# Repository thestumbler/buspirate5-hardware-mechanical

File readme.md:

# Bus Pirate 5, Mechanical Envelope Drawing

This repo has some scripts to enable semi-automatic preparation of
mechanical envelope drawing of the Bus Pirate 5 enclosure. 

## Background

The enclosure is designed in OpenSCAD. Getting 2D dimension drawings out
of OpenSCAD, while possible, is awkward ( see this [repo](
https://github.com/pwpearson/dimensional-drawings.git) for example ).
It is straightforward to make an XY projection or cut of an object. 
And KiCad has basic dimensioning for several versions now. So the
approach taken is

(1) create projections using OpenSCAD design
(2) save as DXF files, import into KiCad
(3) add dimensioning in KiCad

## OpenSCAD Projections

The file `make2d.scad` contains the for projecting the
different views. The code is organized as follows:

* module fiducial()
* module scad2kicad()
* module scad2kicad_sides()
* module project()
* module project_aux_side()
* module project_usb_side()
* // Main Slicing Code...

In summary, this requires the following 
operations (details are in the code):

* X-Y translation
* Mirroring
* Rotation
* Matching origin

This code could be put directly in the SCAD file. But there are several
versions to deal with, and it would be nice to keep this code separate.
The code is substantially independent, although it reaches into the
enclosure file to get the objects needed.

The only problem encountered with this approach is with OpenSCAD
importing of modules.

* If you `include` a file, you pickup all the modules and variables, but
  you also get any objects that are drawn in the main code.

* If you `use` a file, you get all the modules, any objects are not
  drawn, but you don't get the variables.

I don't have a solution for this. What I did was a compromise. I moved
all the parameters in the enclosure design to a file `params.scad`. 
If this is adopted, then all the versions of the enclosure would need to
carve out the variables into separate parameter files.

One other option is to organize the enclosure files so they don't create
any mainline objects without a control flag. This makes is easy to
include the files as-is, and use flags in the user customizer panel. See
`make2d.scad` for an example of this.

## KiCad Import

Importing the DXF files into KiCad is made easy by positioning the XY
projections in OpenSCAD so they match the exact placement of the PCB in
KiCAD. You can just import the files referenced to (0,0) and there is no
need to use interactive placement.

Four new layers are created as follows:

* User1  Bottom XY projection
* User2  Top and Sides projections
* User3  Bottom dimensions
* User4  Top and Sides dimensions

Dimensions are made by hand. 

## Revisions

All these four layers are kept in a separete PCB design `mech`. This
deisng only has four layers, the four user layers. If you make a new
BusPirate revision, you to the `append board` operation to add these to
the design.

If there are changes to the enclosure design, you have to remake the DXF
files and reimport them into KiCad. For most changes, it is easy to 
tweak the dimension layers to match any changes. The shell script
`make2d.sh` creates all four DXF files at once. 

As currently coded, you meed to manually edit the include statement in
make2d.scad (the target file of an include/use cannot be a variable).

# Resources

- [Download the latest firmware build](https://forum.buspirate.com/t/bus-pirate-5-auto-build-main-branch/20/99999)
- [Get help and chat in the forum](https://forum.buspirate.com/)
- [Firmware documentation](https://firmware.buspirate.com/) ([source](https://github.com/DangerousPrototypes/BusPirate5-docs-firmware))
- [Hardware documentation](https://hardware.buspirate.com/) ([source](https://github.com/DangerousPrototypes/BusPirate5-docs-hardware))
- [Hardware repo](https://github.com/DangerousPrototypes/BusPirate5-hardware)
- [Firmware repo](https://github.com/DangerousPrototypes/BusPirate5-firmware)

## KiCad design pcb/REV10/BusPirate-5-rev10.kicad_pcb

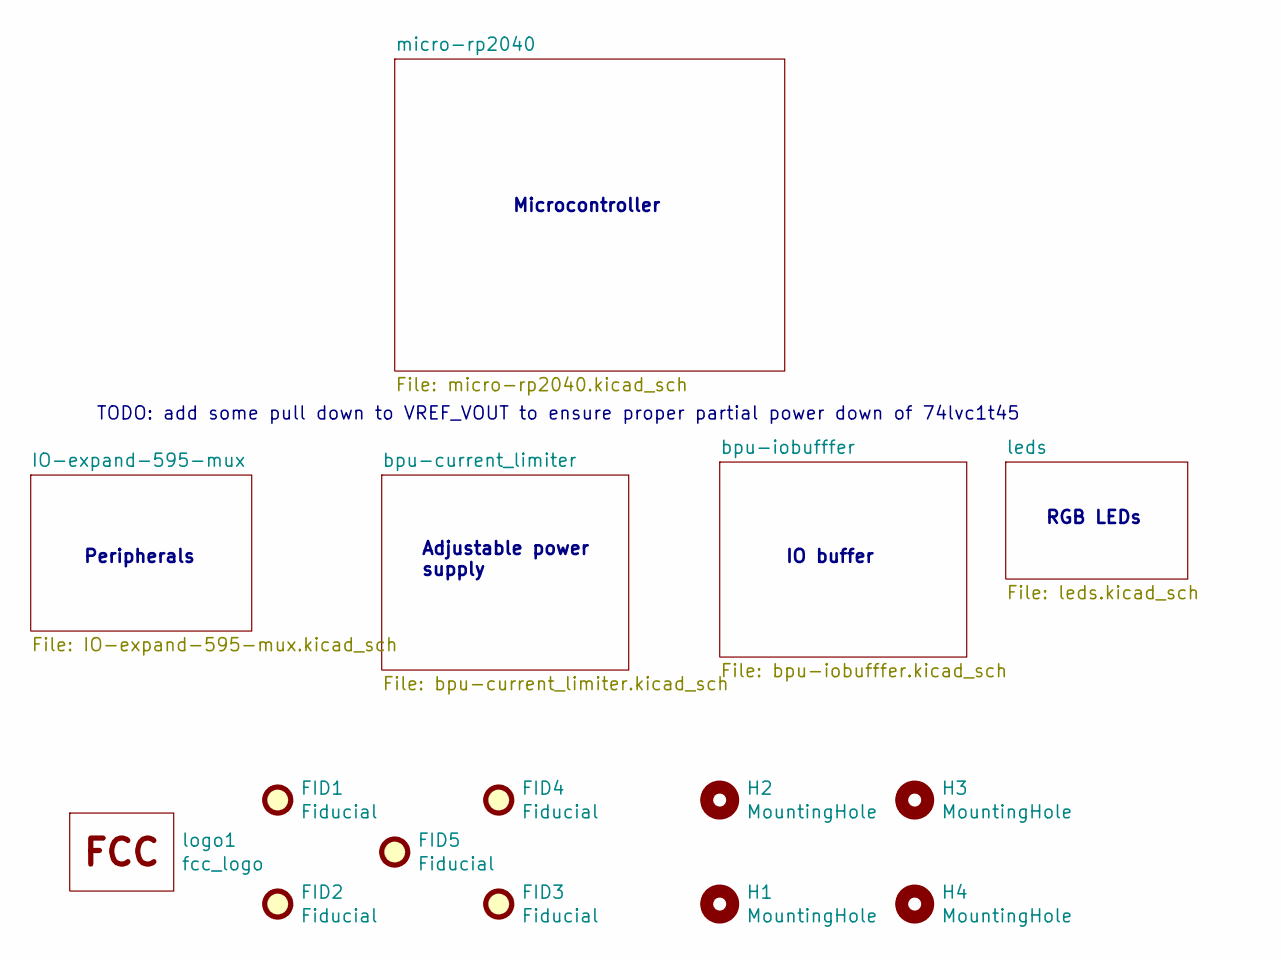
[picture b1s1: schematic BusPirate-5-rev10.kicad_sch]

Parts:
FID1, FID2, FID3, FID4, FID5: Fiducial; Fiducial_1mm_Mask2mm
H1, H2, H3, H4: MountingHole; MountingHole_3.2mm_M3
logo1: fcc_logo; logo_fcc

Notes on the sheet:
Microcontroller
Adjustable power supply
TODO: add some pull down to VREF_VOUT to ensure proper partial power down of 74lvc1t45
IO buffer
Peripherals
RGB LEDs

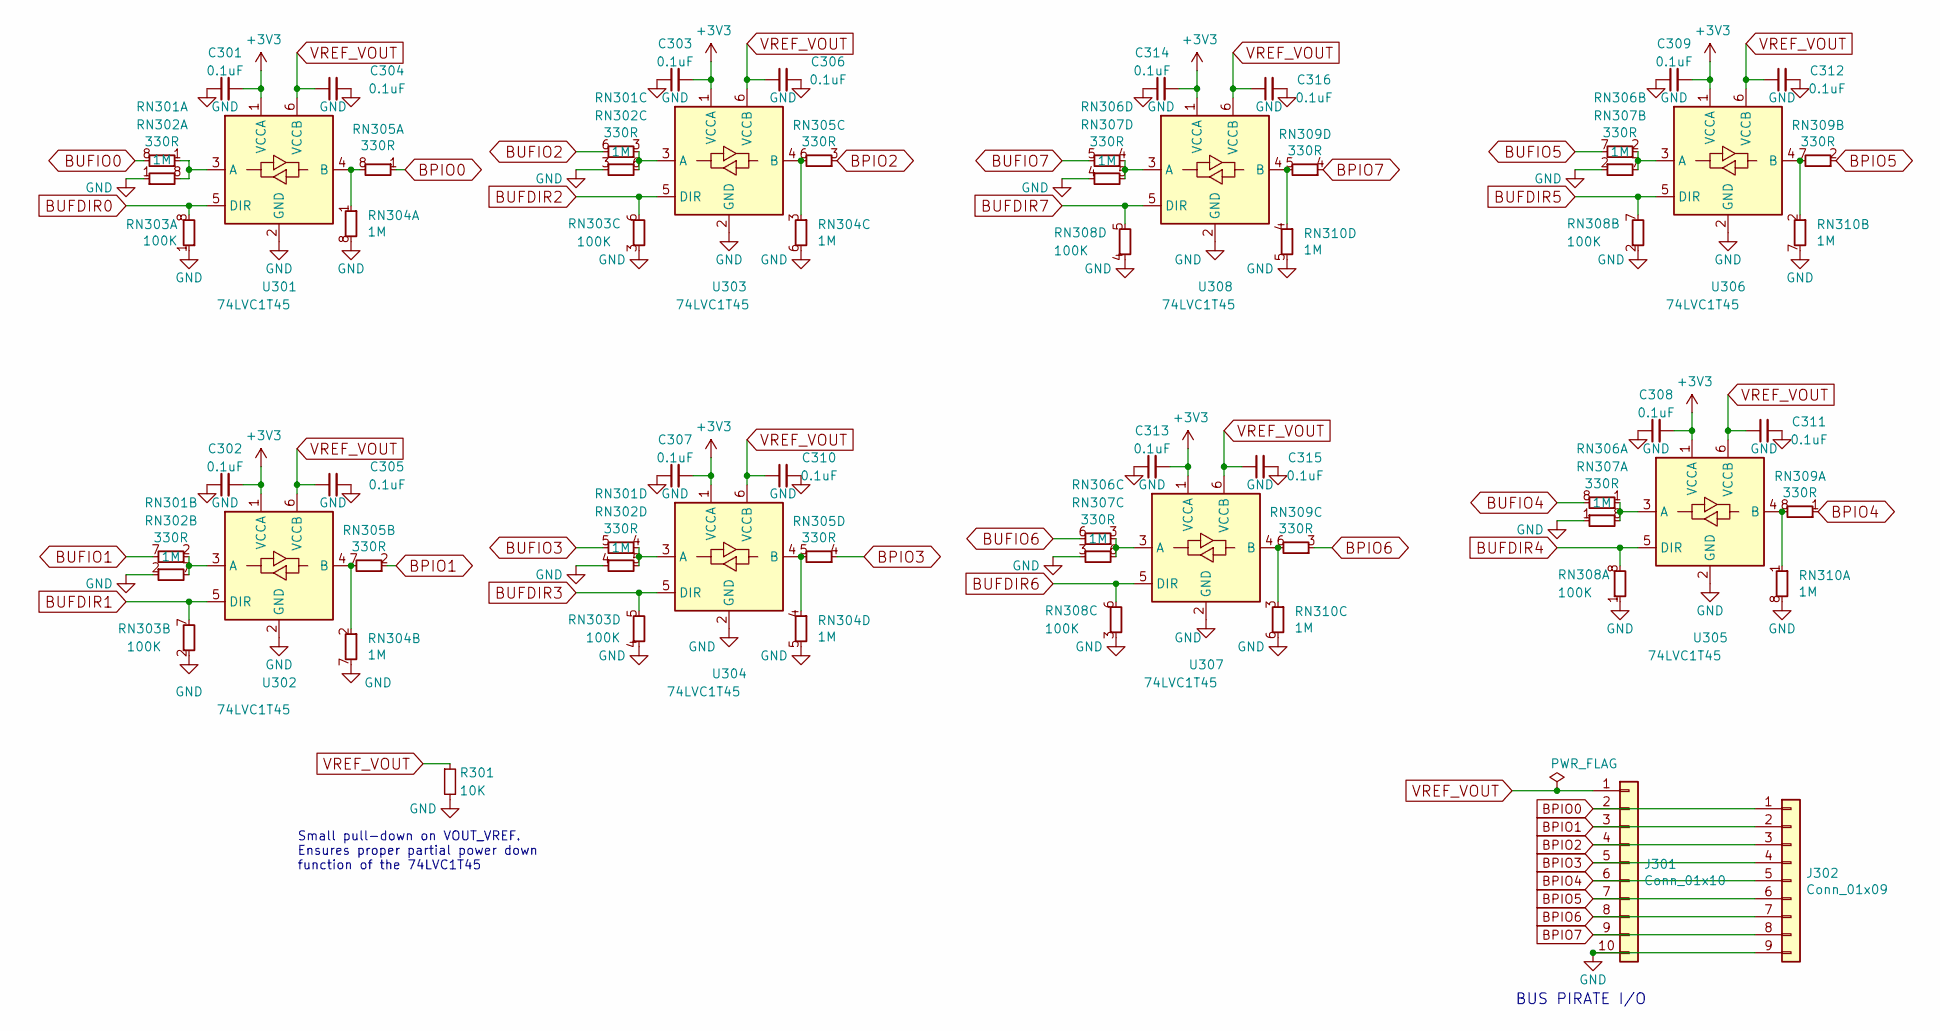
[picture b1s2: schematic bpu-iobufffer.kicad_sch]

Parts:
C301, C302, C303, C304, C305, C306, C307, C308, C309, C310, C311, C312, C313, C314, C315, C316: 0.1uF; C_0402_1005Metric
J301: Conn_01x10; PinHeader_1x10_P2.54mm_Vertical
J302: Conn_01x09; JST_SH_SM09B-SRSS-TB_1x09-1MP_P1.00mm_Horizontal
R301: 10K; R_0402_1005Metric
RN301, RN305, RN306, RN309: 330R; R_Array_Convex_4x0402
RN302, RN304, RN307, RN310: 1M; R_Array_Convex_4x0402
RN303, RN308: 100K; R_Array_Convex_4x0402
U301, U302, U303, U304, U305, U306, U307, U308: 74LVC1T45; SOT-363_SC-70-6

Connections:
+3V3: C301.2, C302.2, C303.2, C307.2, C308.2, C309.2, C313.2, C314.2, U301.1 (VCCA), U302.1 (VCCA), U303.1 (VCCA), U304.1 (VCCA), U305.1 (VCCA), U306.1 (VCCA), U307.1 (VCCA), U308.1 (VCCA); also elsewhere on the board
BPIO0: J301.2, J302.1, RN305.1 (R1.1); also elsewhere on the board
BPIO1: J301.3, J302.2, RN305.2 (R1.1); also elsewhere on the board
BPIO2: J301.4, J302.3, RN305.3 (R1.1); also elsewhere on the board
BPIO3: J301.5, J302.4, RN305.4 (R1.1); also elsewhere on the board
BPIO4: J301.6, J302.5, RN309.1 (R1.1); also elsewhere on the board
BPIO5: J301.7, J302.6, RN309.2 (R1.1); also elsewhere on the board
BPIO6: J301.8, J302.7, RN309.3 (R1.1); also elsewhere on the board
BPIO7: J301.9, J302.8, RN309.4 (R1.1); also elsewhere on the board
BUFDIR0: RN303.8 (R1.8), U301.5 (DIR); also elsewhere on the board
BUFDIR1: RN303.7 (R1.8), U302.5 (DIR); also elsewhere on the board
BUFDIR2: RN303.6 (R1.8), U303.5 (DIR); also elsewhere on the board
BUFDIR3: RN303.5 (R1.8), U304.5 (DIR); also elsewhere on the board
BUFDIR4: RN308.8 (R1.8), U305.5 (DIR); also elsewhere on the board
BUFDIR5: RN308.7 (R1.8), U306.5 (DIR); also elsewhere on the board
BUFDIR6: RN308.6 (R1.8), U307.5 (DIR); also elsewhere on the board
BUFDIR7: RN308.5 (R1.8), U308.5 (DIR); also elsewhere on the board
BUFIO0: RN301.8 (R1.8); also elsewhere on the board
BUFIO1: RN301.7 (R1.8); also elsewhere on the board
BUFIO2: RN301.6 (R1.8); also elsewhere on the board
BUFIO3: RN301.5 (R1.8); also elsewhere on the board
BUFIO4: RN306.8 (R1.8); also elsewhere on the board
BUFIO5: RN306.7 (R1.8); also elsewhere on the board
BUFIO6: RN306.6 (R1.8); also elsewhere on the board
BUFIO7: RN306.5 (R1.8); also elsewhere on the board
GND: C301.1, C302.1, C303.1, C304.2, C305.2, C306.2, C307.1, C308.1, C309.1, C310.2, C311.2, C312.2, C313.1, C314.1, C315.2, C316.2, J301.10, J302.9, R301.2, RN302.1 (R1.1), RN302.2 (R1.1), RN302.3 (R1.1), RN302.4 (R1.1), RN303.1 (R1.1), RN303.2 (R1.1), RN303.3 (R1.1), RN303.4 (R1.1), RN304.5 (R1.8), RN304.6 (R1.8), RN304.7 (R1.8), RN304.8 (R1.8), RN307.1 (R1.1), RN307.2 (R1.1), RN307.3 (R1.1), RN307.4 (R1.1), RN308.1 (R1.1), RN308.2 (R1.1), RN308.3 (R1.1), RN308.4 (R1.1), RN310.5 (R1.8), RN310.6 (R1.8), RN310.7 (R1.8), RN310.8 (R1.8), U301.2 (GND), U302.2 (GND), U303.2 (GND), U304.2 (GND), U305.2 (GND), U306.2 (GND), U307.2 (GND), U308.2 (GND); also elsewhere on the board
unnamed: RN301.1 (R1.1), RN302.8 (R1.8), U301.3 (A)
unnamed: RN301.2 (R1.1), RN302.7 (R1.8), U302.3 (A)
unnamed: RN301.3 (R1.1), RN302.6 (R1.8), U303.3 (A)
unnamed: RN301.4 (R1.1), RN302.5 (R1.8), U304.3 (A)
unnamed: RN304.1 (R1.1), RN305.8 (R1.8), U301.4 (B)
unnamed: RN304.2 (R1.1), RN305.7 (R1.8), U302.4 (B)
unnamed: RN304.3 (R1.1), RN305.6 (R1.8), U303.4 (B)
unnamed: RN304.4 (R1.1), RN305.5 (R1.8), U304.4 (B)
unnamed: RN306.1 (R1.1), RN307.8 (R1.8), U305.3 (A)
unnamed: RN306.2 (R1.1), RN307.7 (R1.8), U306.3 (A)
unnamed: RN306.3 (R1.1), RN307.6 (R1.8), U307.3 (A)
unnamed: RN306.4 (R1.1), RN307.5 (R1.8), U308.3 (A)
unnamed: RN309.8 (R1.8), RN310.1 (R1.1), U305.4 (B)
unnamed: RN309.7 (R1.8), RN310.2 (R1.1), U306.4 (B)
unnamed: RN309.6 (R1.8), RN310.3 (R1.1), U307.4 (B)
unnamed: RN309.5 (R1.8), RN310.4 (R1.1), U308.4 (B)
VREF_VOUT: C304.1, C305.1, C306.1, C310.1, C311.1, C312.1, C315.1, C316.1, J301.1, R301.1, U301.6 (VCCB), U302.6 (VCCB), U303.6 (VCCB), U304.6 (VCCB), U305.6 (VCCB), U306.6 (VCCB), U307.6 (VCCB), U308.6 (VCCB); also elsewhere on the board

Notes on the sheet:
Small pull-down on VOUT_VREF. Ensures proper partial power down function of the 74LVC1T45
BUS PIRATE I/O

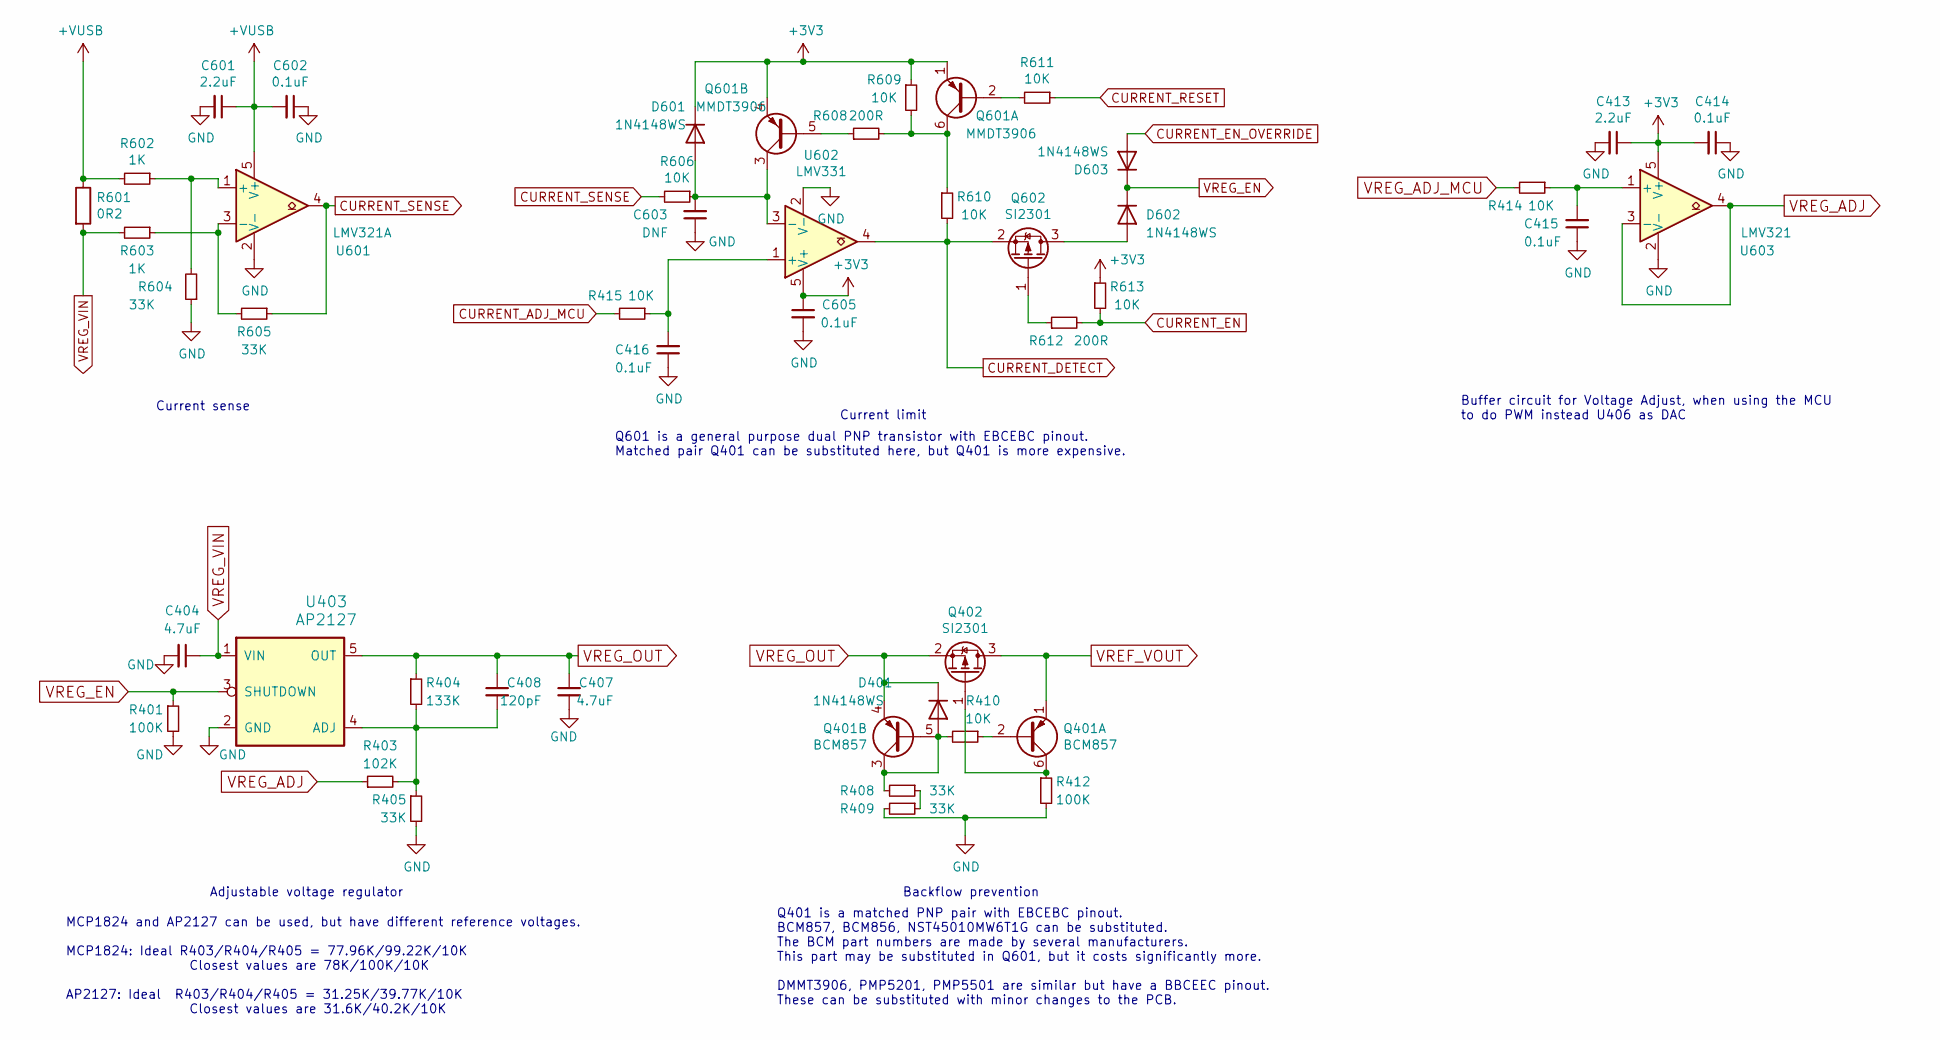
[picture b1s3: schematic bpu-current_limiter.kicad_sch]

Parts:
C404, C407: 4.7uF; C_0402_1005Metric
C408: 120pF; C_0402_1005Metric
C413, C601: 2.2uF; C_0402_1005Metric
C414, C415, C416, C602, C605: 0.1uF; C_0402_1005Metric
C603: DNF; C_0402_1005Metric
D401, D601, D602, D603: 1N4148WS; D_SOD-523
Q401: BCM857; SOT-363_SC-70-6
Q402, Q602: SI2301; SOT-523
Q601: MMDT3906; SOT-363_SC-70-6
R401, R412: 100K; R_0402_1005Metric
R403: 102K; R_0402_1005Metric
R404: 133K; R_0402_1005Metric
R405, R408, R409, R604, R605: 33K; R_0402_1005Metric
R410, R414, R415, R606, R609, R610, R611, R613: 10K; R_0402_1005Metric
R601: 0R2; R_2512_6332Metric_Pad1.40x3.35mm_HandSolder
R602, R603: 1K; R_0402_1005Metric
R608, R612: 200R; R_0402_1005Metric
U403: AP2127; SOT-23-5
U601: LMV321A; SOT-23-5
U602: LMV331; SOT-23-5
U603: LMV321; SOT-23-5

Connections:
+3V3: C413.1, C414.2, C605.1, D601.1 (K), Q601.1 (E1), Q601.4 (E2), R609.1, R613.1, U602.5 (V+), U603.5 (V+); also elsewhere on the board
+VUSB: C601.1, C602.2, R601.1, R602.2, U601.5 (V+); also elsewhere on the board
CURRENT_ADJ_MCU: R415.2; also elsewhere on the board
CURRENT_DETECT: Q602.2 (S), R610.2, U602.4; also elsewhere on the board
CURRENT_EN: R612.2, R613.2; also elsewhere on the board
CURRENT_EN_OVERRIDE: D603.2 (A); also elsewhere on the board
CURRENT_RESET: R611.1; also elsewhere on the board
CURRENT_SENSE: R605.1, R606.2, U601.4; also elsewhere on the board
GND: C404.2, C407.2, C413.2, C414.1, C415.1, C416.1, C601.2, C602.1, C603.1, C605.2, R401.2, R405.2, R409.2, R412.2, R604.1, U403.2 (GND), U601.2 (V-), U602.2 (V-), U603.2 (V-); also elsewhere on the board
unnamed: D401.2 (A), Q401.3 (C2), Q401.5 (B2), R408.2, R410.2
unnamed: C603.2, D601.2 (A), Q601.3 (C2), R606.1, U602.3 (-)
unnamed: D602.2 (A), Q602.3 (D)
unnamed: Q401.2 (B1), R410.1
unnamed: Q401.6 (C1), Q402.1 (G), R412.1
unnamed: Q601.2 (B1), R611.2
unnamed: Q601.6 (C1), R608.2, R609.2, R610.1
unnamed: Q601.5 (B2), R608.1
unnamed: Q602.1 (G), R612.1
unnamed: R408.1, R409.1
unnamed: C408.2, R403.2, R404.2, R405.1, U403.4 (ADJ)
unnamed: R602.1, R604.2, U601.1 (+)
unnamed: R603.1, R605.2, U601.3 (-)
unnamed: C416.2, R415.1, U602.1 (+)
unnamed: C415.2, R414.1, U603.1 (+)
VREF_VOUT: Q401.1 (E1), Q402.3 (D); also elsewhere on the board
VREG_ADJ: R403.1, U603.3 (-), U603.4
VREG_ADJ_MCU: R414.2; also elsewhere on the board
VREG_EN: D602.1 (K), D603.1 (K), R401.1, U403.3 (SHUTDOWN)
VREG_OUT: C407.1, C408.1, D401.1 (K), Q401.4 (E2), Q402.2 (S), R404.1, U403.5 (OUT); also elsewhere on the board
VREG_VIN: C404.1, R601.2, R603.2, U403.1 (VIN)

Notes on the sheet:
Adjustable voltage regulator
Buffer circuit for Voltage Adjust, when using the MCU to do PWM instead U406 as DAC
Current sense
Backflow prevention
MCP1824 and AP2127 can be used, but have different reference voltages. MCP1824: Ideal R403/R404/R405 = 77.96K/99.22K/10K Closest values are 78K/100K/10K AP2127: Ideal R403/R404/R405 = 31.25K/39.77K/10K Closest values are 31.6K/40.2K/10K
Current limit
Q401 is a matched PNP pair with EBCEBC pinout. BCM857, BCM856, NST45010MW6T1G can be substituted. The BCM part numbers are made by several manufacturers. This part may be substituted in Q601, but it costs significantly more. DMMT3906, PMP5201, PMP5501 are similar but have a BBCEEC pinout. These can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
Q601 is a general purpose dual PNP transistor with EBCEBC pinout. Matched pair Q401 can be substituted here, but Q401 is more expensive.

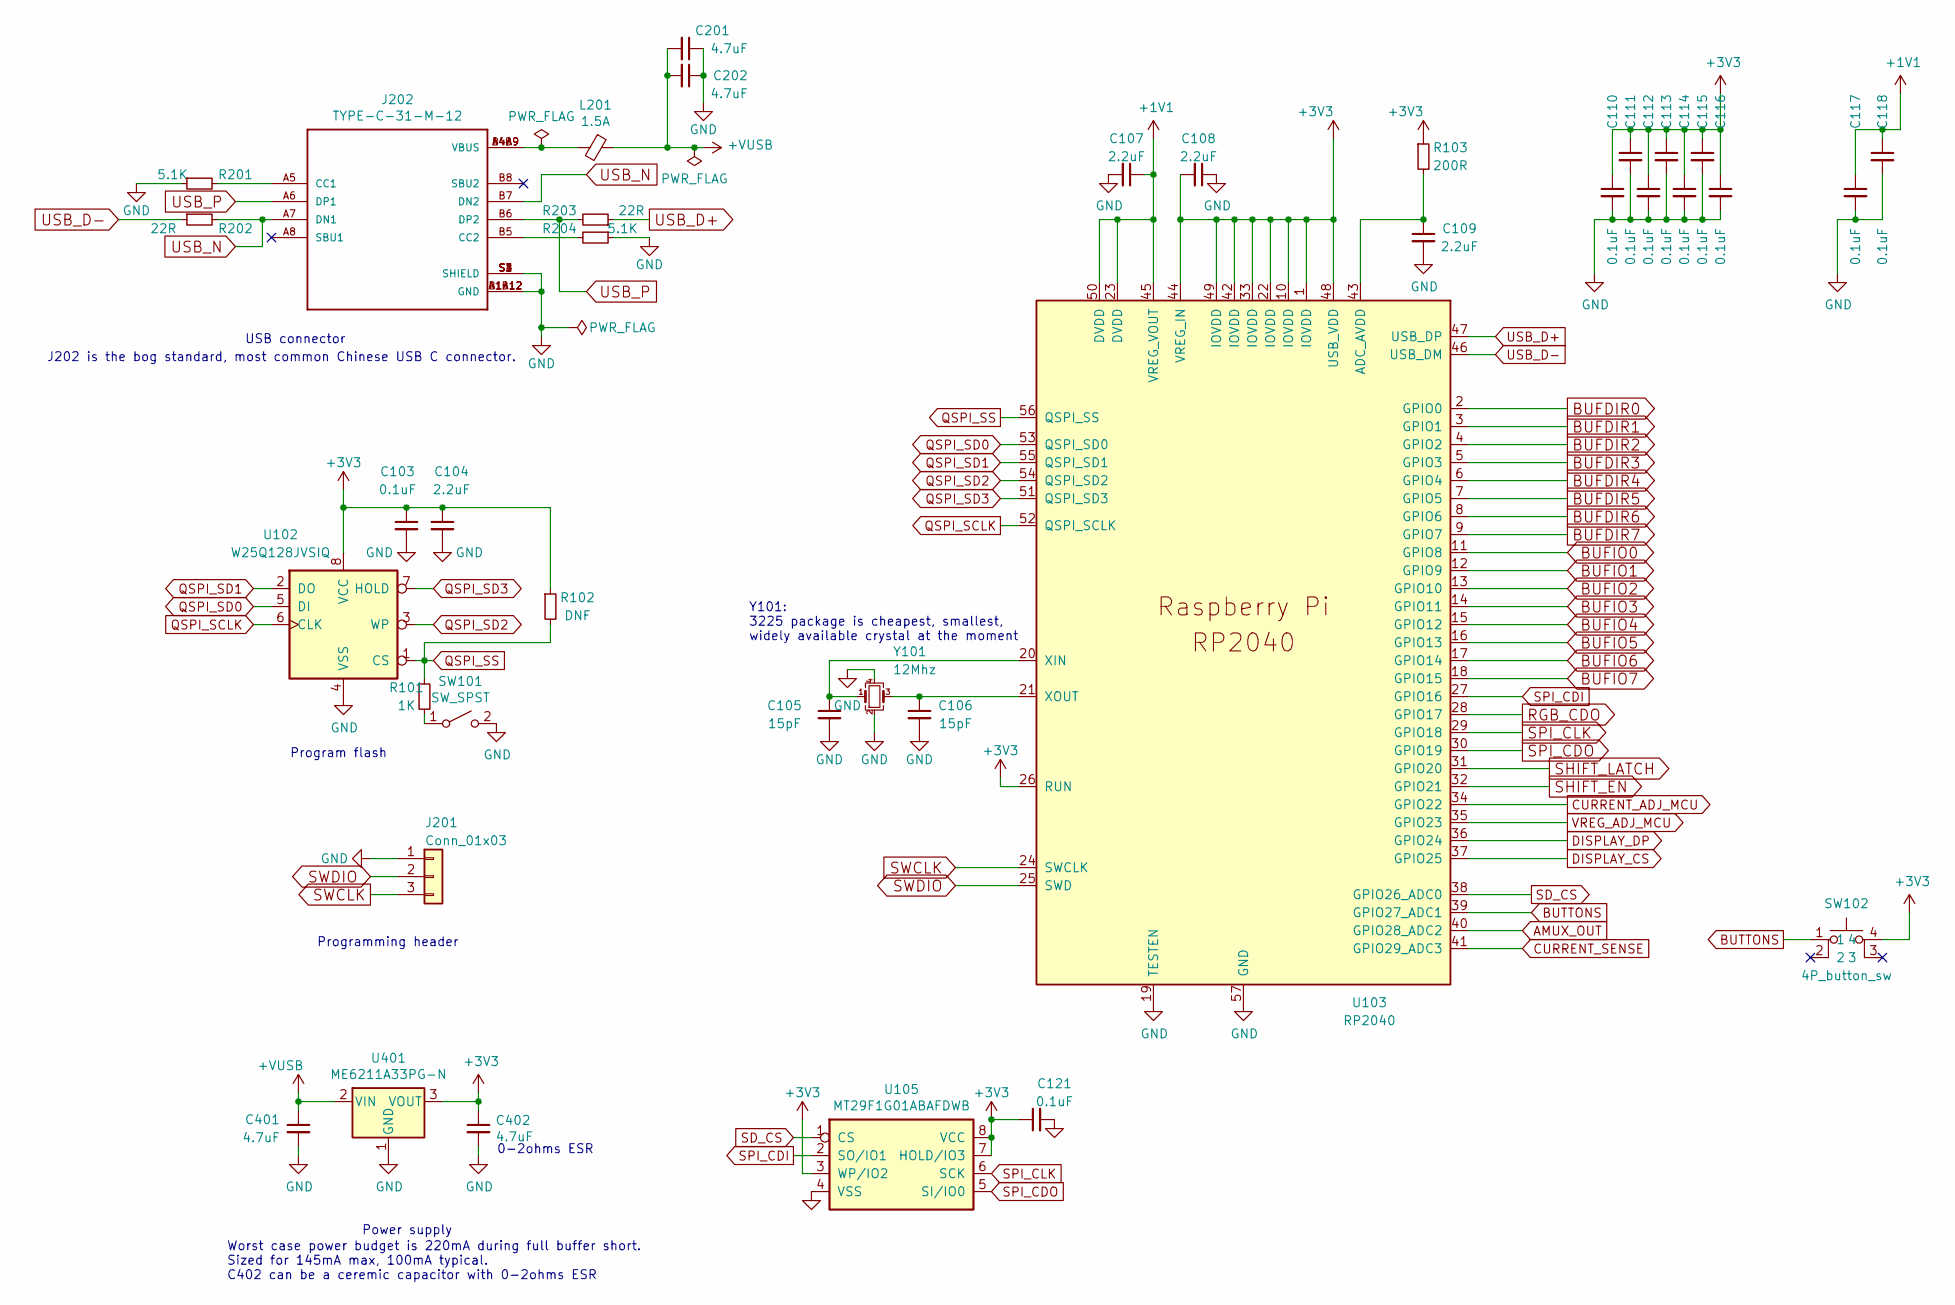
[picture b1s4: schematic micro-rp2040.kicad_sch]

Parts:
C103, C110, C111, C112, C113, C114, C115, C116, C117, C118, C121: 0.1uF; C_0402_1005Metric
C104, C107, C108, C109: 2.2uF; C_0402_1005Metric
C105, C106: 15pF; C_0402_1005Metric
C201, C202, C401, C402: 4.7uF; C_0402_1005Metric
J201: Conn_01x03; PinSocket_1x03_P2.54mm_Vertical
J202: TYPE-C-31-M-12; HRO_TYPE-C-31-M-12
L201: 1.5A; L_0805_2012Metric
R101: 1K; R_0402_1005Metric
R102: DNF; R_0402_1005Metric
R103: 200R; R_0402_1005Metric
R201, R204: 5.1K; R_0402_1005Metric
R202, R203: 22R; R_0402_1005Metric
SW101: SW_SPST; SW_SPST_PTS810
SW102: 4P_button_sw; GT-TC026X-HXXX-LX
U102: W25Q128JVSIQ; SOP-8_5.28x5.23mm_P1.27mm
U103: RP2040; RP2040-QFN-56
U105: MT29F1G01ABAFDWB; U-PDFN-8
U401: ME6211A33PG-N; SOT-89-3
Y101: 12Mhz; Crystal_SMD_3225-4Pin_3.2x2.5mm

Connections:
+1V1: C107.1, C117.1, C118.1, U103.23 (DVDD), U103.45 (VREG_VOUT), U103.50 (DVDD)
+3V3: C103.1, C104.1, C108.2, C110.1, C111.1, C112.1, C113.1, C114.1, C115.1, C116.1, C121.1, C402.1, R102.1, R103.1, SW102.4, U102.8 (VCC), U103.1 (IOVDD), U103.10 (IOVDD), U103.22 (IOVDD), U103.26 (RUN), U103.33 (IOVDD), U103.42 (IOVDD), U103.44 (VREG_IN), U103.48 (USB_VDD), U103.49 (IOVDD), U105.3 (WP/IO2), U105.7 (HOLD/IO3), U105.8 (VCC), U401.3 (VOUT); also elsewhere on the board
+VUSB: C201.2, C202.2, C401.1, L201.1, U401.2 (VIN); also elsewhere on the board
AMUX_OUT: U103.40 (GPIO28_ADC2); also elsewhere on the board
BUFDIR0: U103.2 (GPIO0); also elsewhere on the board
BUFDIR1: U103.3 (GPIO1); also elsewhere on the board
BUFDIR2: U103.4 (GPIO2); also elsewhere on the board
BUFDIR3: U103.5 (GPIO3); also elsewhere on the board
BUFDIR4: U103.6 (GPIO4); also elsewhere on the board
BUFDIR5: U103.7 (GPIO5); also elsewhere on the board
BUFDIR6: U103.8 (GPIO6); also elsewhere on the board
BUFDIR7: U103.9 (GPIO7); also elsewhere on the board
BUFIO0: U103.11 (GPIO8); also elsewhere on the board
BUFIO1: U103.12 (GPIO9); also elsewhere on the board
BUFIO2: U103.13 (GPIO10); also elsewhere on the board
BUFIO3: U103.14 (GPIO11); also elsewhere on the board
BUFIO4: U103.15 (GPIO12); also elsewhere on the board
BUFIO5: U103.16 (GPIO13); also elsewhere on the board
BUFIO6: U103.17 (GPIO14); also elsewhere on the board
BUFIO7: U103.18 (GPIO15); also elsewhere on the board
BUTTONS: SW102.1, U103.39 (GPIO27_ADC1)
CURRENT_ADJ_MCU: U103.34 (GPIO22); also elsewhere on the board
CURRENT_SENSE: U103.41 (GPIO29_ADC3); also elsewhere on the board
DISPLAY_CS: U103.37 (GPIO25); also elsewhere on the board
DISPLAY_DP: U103.36 (GPIO24); also elsewhere on the board
GND: C103.2, C104.2, C105.2, C106.2, C107.2, C108.1, C109.2, C110.2, C111.2, C112.2, C113.2, C114.2, C115.2, C116.2, C117.2, C118.2, C121.2, C201.1, C202.1, C401.2, C402.2, J201.1, J202.A1B12 (GND), J202.B1A12 (GND), J202.S1 (SHIELD), J202.S2 (SHIELD), J202.S3 (SHIELD), J202.S4 (SHIELD), R201.1, R204.1, SW101.2 (B), U102.4 (VSS), U103.19 (TESTEN), U103.57 (GND), U105.4 (VSS), U401.1 (GND), Y101.2, Y101.4; also elsewhere on the board
unnamed: J202.A5 (CC1), R201.2
unnamed: J202.B5 (CC2), R204.2
unnamed: J202.A4B9 (VBUS), J202.B4A9 (VBUS), L201.2
unnamed: R101.2, SW101.1 (A)
unnamed: C109.1, R103.2, U103.43 (ADC_AVDD)
unnamed: C105.1, U103.20 (XIN), Y101.1
unnamed: C106.1, U103.21 (XOUT), Y101.3
QSPI_SCLK: U102.6 (CLK), U103.52 (QSPI_SCLK)
QSPI_SD0: U102.5 (DI), U103.53 (QSPI_SD0)
QSPI_SD1: U102.2 (DO), U103.55 (QSPI_SD1)
QSPI_SD2: U102.3 (WP), U103.54 (QSPI_SD2)
QSPI_SD3: U102.7 (HOLD), U103.51 (QSPI_SD3)
QSPI_SS: R101.1, R102.2, U102.1 (CS), U103.56 (QSPI_SS)
RGB_CDO: U103.28 (GPIO17); also elsewhere on the board
SD_CS: U103.38 (GPIO26_ADC0), U105.1 (CS)
SHIFT_EN: U103.32 (GPIO21); also elsewhere on the board
SHIFT_LATCH: U103.31 (GPIO20); also elsewhere on the board
SPI_CDI: U103.27 (GPIO16), U105.2 (SO/IO1)
SPI_CDO: U103.30 (GPIO19), U105.5 (SI/IO0); also elsewhere on the board
SPI_CLK: U103.29 (GPIO18), U105.6 (SCK); also elsewhere on the board
SWCLK: J201.3, U103.24 (SWCLK)
SWDIO: J201.2, U103.25 (SWD)
USB_D+: R203.1, U103.47 (USB_DP)
USB_D-: R202.1, U103.46 (USB_DM)
USB_N: J202.A7 (DN1), J202.B7 (DN2), R202.2
USB_P: J202.A6 (DP1), J202.B6 (DP2), R203.2
VREG_ADJ_MCU: U103.35 (GPIO23); also elsewhere on the board

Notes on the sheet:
USB connector
Y101: 3225 package is cheapest, smallest, widely available crystal at the moment
Power supply
J202 is the bog standard, most common Chinese USB C connector.
Program flash
Worst case power budget is 220mA during full buffer short. Sized for 145mA max, 100mA typical. C402 can be a ceremic capacitor with 0-2ohms ESR
Programming header
0-2ohms ESR

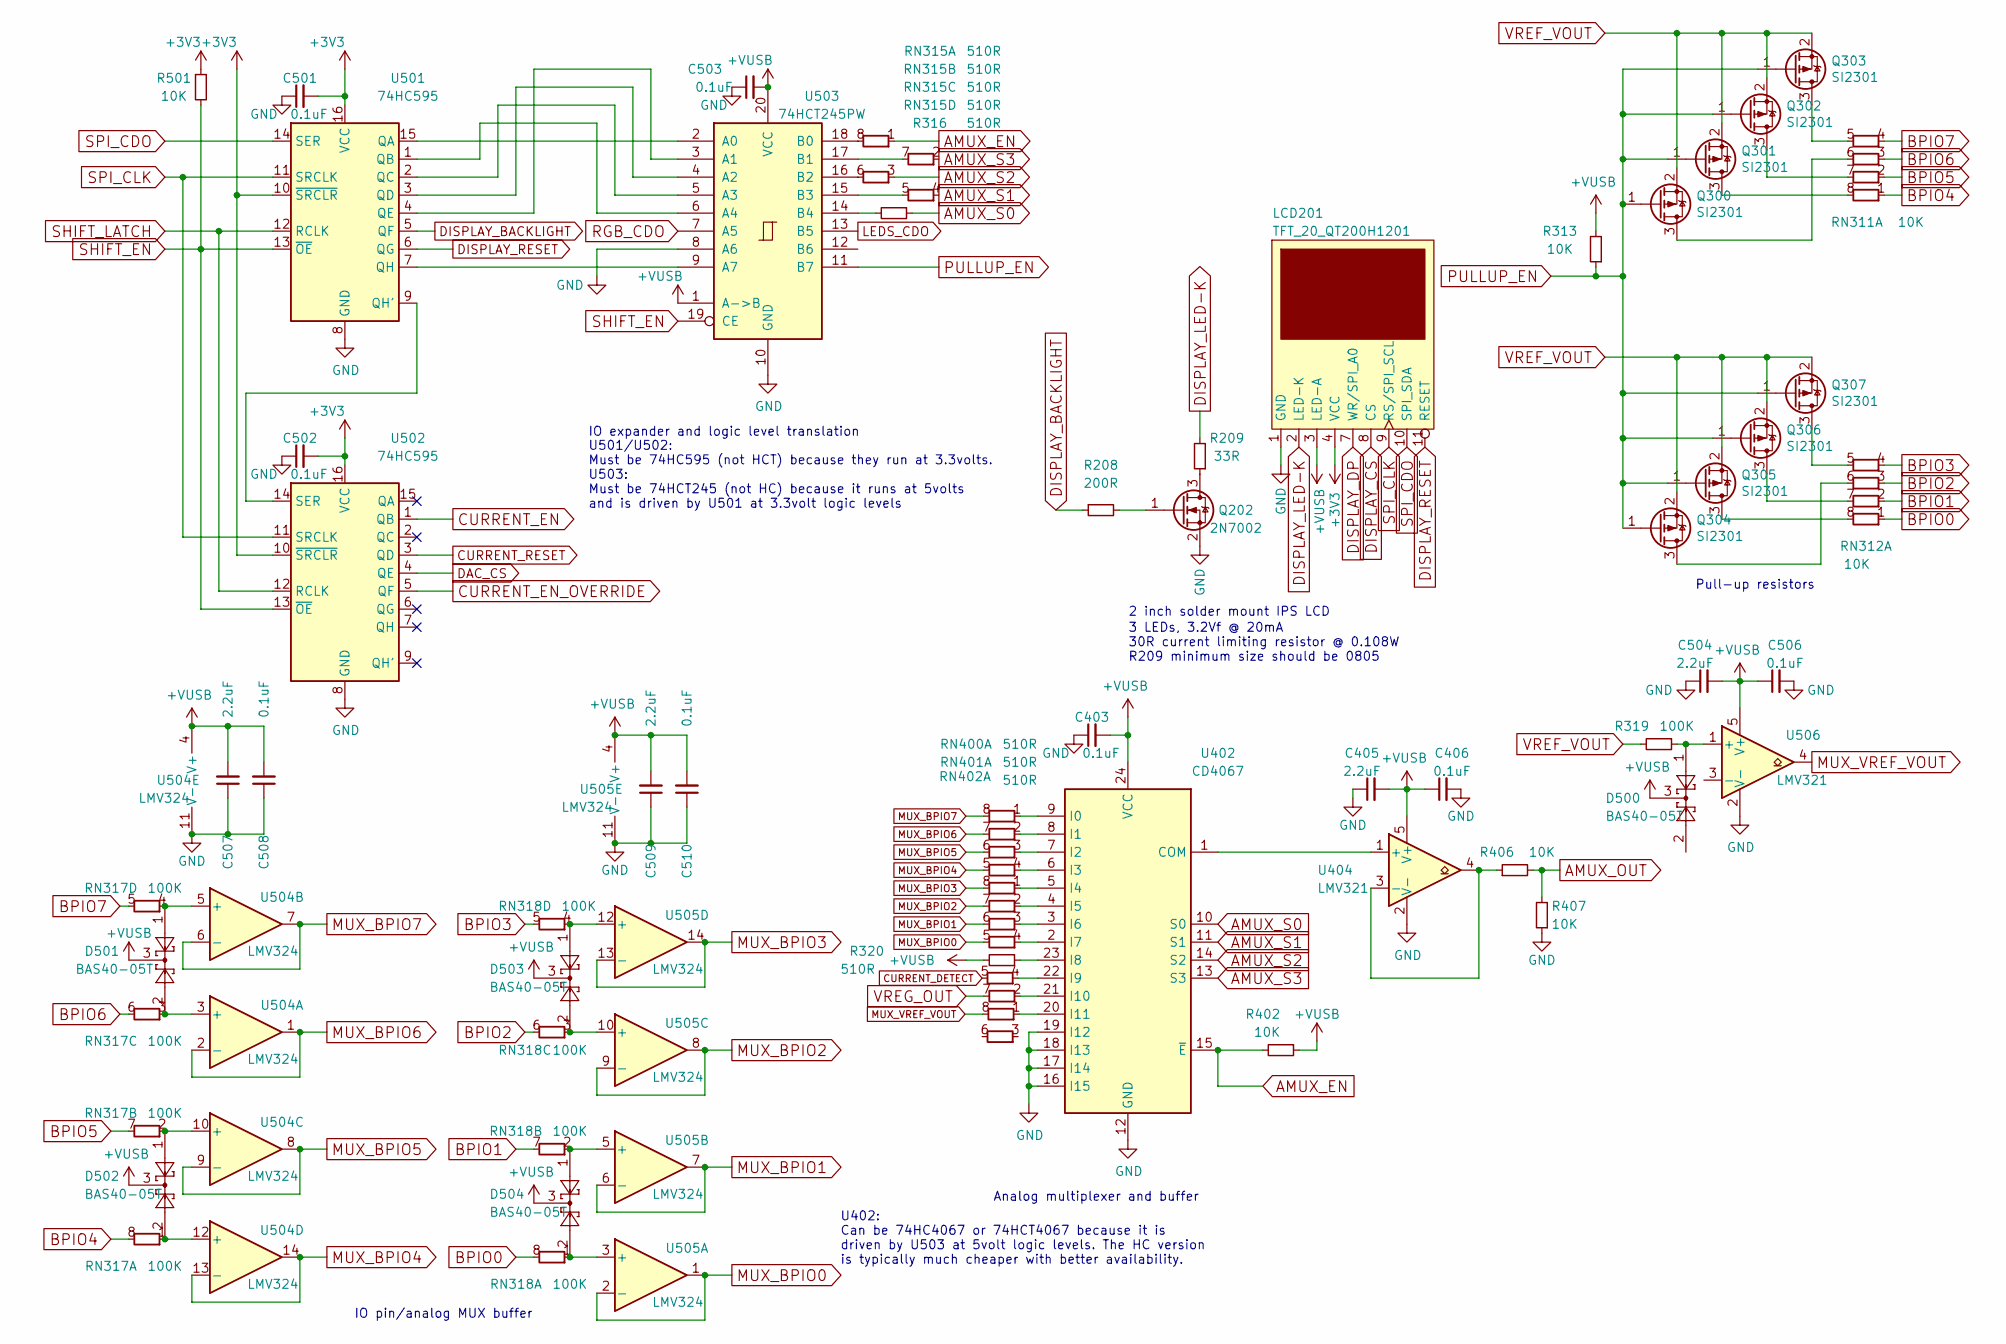
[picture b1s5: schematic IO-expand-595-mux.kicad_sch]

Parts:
C403, C406, C501, C502, C503, C506, C508, C510: 0.1uF; C_0402_1005Metric
C405, C504, C507, C509: 2.2uF; C_0402_1005Metric
D500, D501, D502, D503, D504: BAS40-05T; SOT-523
LCD201: TFT_20_QT200H1201
Q202: 2N7002; SOT-23
Q300, Q301, Q302, Q303, Q304, Q305, Q306, Q307: SI2301; SOT-523
R208: 200R; R_0402_1005Metric
R209: 33R; R_0805_2012Metric
R313, R402, R406, R407, R501: 10K; R_0402_1005Metric
R316, R320: 510R; R_0402_1005Metric
R319: 100K; R_0402_1005Metric
RN311, RN312: 10K; R_Array_Convex_4x0402
RN315, RN400, RN401, RN402: 510R; R_Array_Convex_4x0402
RN317, RN318: 100K; R_Array_Convex_4x0402
U402: CD4067; TSSOP-24_4.4x7.8mm_P0.65mm
U404, U506: LMV321; SOT-23-5
U501, U502: 74HC595; TSSOP-16_4.4x5mm_P0.65mm
U503: 74HCT245PW; TSSOP-20_4.4x6.5mm_P0.65mm
U504, U505: LMV324; TSSOP-14_4.4x5mm_P0.65mm

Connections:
+3V3: C501.2, C502.2, LCD201.4 (VCC), R501.1, U501.10 (~SRCLR), U501.16 (VCC), U502.10 (~SRCLR), U502.16 (VCC); also elsewhere on the board
+VUSB: C403.2, C405.2, C406.1, C503.2, C504.2, C506.1, C507.2, C508.2, C509.2, C510.2, D500.3, D501.3, D502.3, D503.3, D504.3, LCD201.3 (LED-A), R313.2, R320.2, R402.1, U402.24 (VCC), U404.5 (V+), U503.1 (A->B), U503.20 (VCC), U504.4 (V+), U505.4 (V+), U506.5 (V+); also elsewhere on the board
AMUX_EN: R402.2, RN315.1 (R1.1), U402.15 (~E)
AMUX_OUT: R406.2, R407.2; also elsewhere on the board
AMUX_S0: R316.1, U402.10 (S0)
AMUX_S1: RN315.4 (R1.1), U402.11 (S1)
AMUX_S2: RN315.3 (R1.1), U402.14 (S2)
AMUX_S3: RN315.2 (R1.1), U402.13 (S3)
BPIO0: RN312.1 (R1.1), RN318.8 (R1.8); also elsewhere on the board
BPIO1: RN312.2 (R1.1), RN318.7 (R1.8); also elsewhere on the board
BPIO2: RN312.3 (R1.1), RN318.6 (R1.8); also elsewhere on the board
BPIO3: RN312.4 (R1.1), RN318.5 (R1.8); also elsewhere on the board
BPIO4: RN311.1 (R1.1), RN317.8 (R1.8); also elsewhere on the board
BPIO5: RN311.2 (R1.1), RN317.7 (R1.8); also elsewhere on the board
BPIO6: RN311.3 (R1.1), RN317.6 (R1.8); also elsewhere on the board
BPIO7: RN311.4 (R1.1), RN317.5 (R1.8); also elsewhere on the board
CURRENT_DETECT: RN402.5 (R1.8); also elsewhere on the board
CURRENT_EN: U502.1 (QB); also elsewhere on the board
CURRENT_EN_OVERRIDE: U502.5 (QF); also elsewhere on the board
CURRENT_RESET: U502.3 (QD); also elsewhere on the board
DAC_CS: U502.4 (QE)
DISPLAY_BACKLIGHT: R208.1, U501.5 (QF)
DISPLAY_CS: LCD201.8 (CS); also elsewhere on the board
DISPLAY_DP: LCD201.7 (WR/SPI_A0); also elsewhere on the board
DISPLAY_LED-K: LCD201.2 (LED-K), R209.2
DISPLAY_RESET: LCD201.11 (RESET), U501.6 (QG)
GND: C403.1, C405.1, C406.2, C501.1, C502.1, C503.1, C504.1, C506.2, C507.1, C508.1, C509.1, C510.1, LCD201.1 (GND), LCD201.5 (GND), LCD201.6 (GND), LCD201.12 (GND), Q202.2 (S), R407.1, U402.12 (GND), U402.16 (I15), U402.17 (I14), U402.18 (I13), U402.19 (I12), U404.2 (V-), U501.8 (GND), U502.8 (GND), U503.8 (A6), U503.10 (GND), U504.11 (V-), U505.11 (V-), U506.2 (V-); also elsewhere on the board
LEDS_CDO: U503.13 (B5); also elsewhere on the board
MUX_BPIO0: RN401.5 (R1.8), U505.1, U505.2 (-)
MUX_BPIO1: RN401.6 (R1.8), U505.6 (-), U505.7
MUX_BPIO2: RN401.7 (R1.8), U505.8, U505.9 (-)
MUX_BPIO3: RN401.8 (R1.8), U505.13 (-), U505.14
MUX_BPIO4: RN400.5 (R1.8), U504.13 (-), U504.14
MUX_BPIO5: RN400.6 (R1.8), U504.8, U504.9 (-)
MUX_BPIO6: RN400.7 (R1.8), U504.1, U504.2 (-)
MUX_BPIO7: RN400.8 (R1.8), U504.6 (-), U504.7
MUX_VREF_VOUT: RN402.8 (R1.8), U506.4
unnamed: Q202.3 (D), R209.1
unnamed: Q202.1 (G), R208.2
unnamed: Q300.3 (D), RN311.6 (R1.8)
unnamed: Q301.3 (D), RN311.8 (R1.8)
unnamed: Q302.3 (D), RN311.7 (R1.8)
unnamed: Q303.3 (D), RN311.5 (R1.8)
unnamed: Q304.3 (D), RN312.6 (R1.8)
unnamed: Q305.3 (D), RN312.8 (R1.8)
unnamed: Q306.3 (D), RN312.7 (R1.8)
unnamed: Q307.3 (D), RN312.5 (R1.8)
unnamed: RN315.8 (R1.8), U503.18 (B0)
unnamed: RN315.7 (R1.8), U503.17 (B1)
unnamed: RN315.6 (R1.8), U503.16 (B2)
unnamed: RN315.5 (R1.8), U503.15 (B3)
unnamed: D502.2, RN317.1 (R1.1), U504.12 (+)
unnamed: D502.1, RN317.2 (R1.1), U504.10 (+)
unnamed: D501.2, RN317.3 (R1.1), U504.3 (+)
unnamed: D501.1, RN317.4 (R1.1), U504.5 (+)
unnamed: D504.2, RN318.1 (R1.1), U505.3 (+)
unnamed: D504.1, RN318.2 (R1.1), U505.5 (+)
unnamed: D503.2, RN318.3 (R1.1), U505.10 (+)
unnamed: D503.1, RN318.4 (R1.1), U505.12 (+)
unnamed: RN400.1 (R1.1), U402.9 (I0)
unnamed: RN400.2 (R1.1), U402.8 (I1)
unnamed: RN400.3 (R1.1), U402.7 (I2)
unnamed: RN400.4 (R1.1), U402.6 (I3)
unnamed: RN401.1 (R1.1), U402.5 (I4)
unnamed: RN401.2 (R1.1), U402.4 (I5)
unnamed: RN401.3 (R1.1), U402.3 (I6)
unnamed: RN401.4 (R1.1), U402.2 (I7)
unnamed: RN402.1 (R1.1), U402.20 (I11)
unnamed: RN402.2 (R1.1), U402.21 (I10)
unnamed: RN402.4 (R1.1), U402.22 (I9)
unnamed: U402.1 (COM), U404.1 (+)
unnamed: R320.1, U402.23 (I8)
unnamed: R406.1, U404.3 (-), U404.4
unnamed: U501.15 (QA), U503.2 (A0)
unnamed: U501.1 (QB), U503.6 (A4)
unnamed: U501.2 (QC), U503.5 (A3)
unnamed: U501.3 (QD), U503.4 (A2)
unnamed: U501.4 (QE), U503.3 (A1)
unnamed: U501.9 (QH'), U502.14 (SER)
unnamed: U501.7 (QH), U503.9 (A7)
unnamed: R316.2, U503.14 (B4)
unnamed: D500.1, R319.1, U506.1 (+)
PULLUP_EN: Q300.1 (G), Q301.1 (G), Q302.1 (G), Q303.1 (G), Q304.1 (G), Q305.1 (G), Q306.1 (G), Q307.1 (G), R313.1, U503.11 (B7)
RGB_CDO: U503.7 (A5); also elsewhere on the board
SHIFT_EN: R501.2, U501.13 (~OE), U502.13 (~OE), U503.19 (CE); also elsewhere on the board
SHIFT_LATCH: U501.12 (RCLK), U502.12 (RCLK); also elsewhere on the board
SPI_CDO: LCD201.10 (SPI_SDA), U501.14 (SER); also elsewhere on the board
SPI_CLK: LCD201.9 (RS/SPI_SCL), U501.11 (SRCLK), U502.11 (SRCLK); also elsewhere on the board
VREF_VOUT: Q300.2 (S), Q301.2 (S), Q302.2 (S), Q303.2 (S), Q304.2 (S), Q305.2 (S), Q306.2 (S), Q307.2 (S), R319.2; also elsewhere on the board
VREG_OUT: RN402.7 (R1.8); also elsewhere on the board

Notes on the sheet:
IO expander and logic level translation
Analog multiplexer and buffer
U402: Can be 74HC4067 or 74HCT4067 because it is driven by U503 at 5volt logic levels. The HC version is typically much cheaper with better availability.
IO pin/analog MUX buffer
3 LEDs, 3.2Vf @ 20mA 30R current limiting resistor @ 0.108W R209 minimum size should be 0805
2 inch solder mount IPS LCD
U501/U502: Must be 74HC595 (not HCT) because they run at 3.3volts. U503: Must be 74HCT245 (not HC) because it runs at 5volts and is driven by U501 at 3.3volt logic levels
Pull-up resistors
